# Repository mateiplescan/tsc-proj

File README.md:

# OpenBook &copy; Matei-Bogdan Plescan 2025

## Diagrama bloc

## Randare 3D

## Bill of Materials

| Piesă                                      | Qty                                                                                             | Datasheet | Aprovizionare  |
|----------------------------------------------|---------------------------------------------------------------------------------------------------|----------------|-----------------|
| ADAFRUIT_CHIP-LED0603                        | 1                                                                                           | [Link](https://www.snapeda.com/parts/KP-1608SURCK/Kingbright/datasheet/)      | [Link](https://www.arrow.com/en/products/kp-1608surck/kingbright?utm_campaign=arrow_snapeda_q32020&utm_currency=USD&utm_term=KP-1608SURCK&utm_content=inpart_link_download&region=europe&utm_source=snapeda&utm_medium=aggregator)       |
| SJ                                           | 1                                                                                               | [Link](https://grabcad.com/library/solder-jumpers-1)      | [Link](https://grabcad.com/library/solder-jumpers-1)       |
| ESP32_WROVER_EAGLE-LTSPICE_R0402             | 24                                                                                       | [Link](https://ro.mouser.com/ProductDetail/YAGEO/RC0402FR-07100KL?qs=mnq%2FyloZIXzTlUn7JAHSWg%3D%3D)      | [Link](https://ro.mouser.com/ProductDetail/YAGEO/RC0402FR-07100KL?qs=mnq%2FyloZIXzTlUn7JAHSWg%3D%3D)       |
| ESP32_WROVER_EAGLE-LTSPICE_C0402             | 26                                                           | [Link](https://eu.mouser.com/datasheet/2/447/upy_gphc_x5r_4v_to_50v-3461255.pdf)      | [Link](https://eu.mouser.com/ProductDetail/YAGEO/CC0402MRX5R5BB106?qs=zEY9bCHj09eCmUJdZuS5Lg%3D%3D)       |
| RCL_CT3528                                   | 1                                                                                                 | [Link](https://ro.mouser.com/ProductDetail/KEMET/T491B107M006AT?qs=U312oeP%2FpiHOgyk6KO2m0g%3D%3D)      | [Link](https://ro.mouser.com/ProductDetail/KEMET/T491B107M006AT?qs=U312oeP%2FpiHOgyk6KO2m0g%3D%3D)       |
| 112ATAARR03ATTEND                            | 1                                                                                                 | [Link](https://store.comet.bg/download-file.php?id=27596)      | [Link](https://store.comet.srl.ro/Catalogue/Product/43497/)       |
| ESP32_WROVER_SPARKFUN-DISCRETESEMI_SOT23-3    | 2                                                                                             | [Link](https://www.diodes.com/assets/Datasheets/DMG2305UX.pdf)      | [Link](https://eu.mouser.com/ProductDetail/Diodes-Incorporated/DMG2305UX-7?qs=L1DZKBg7t5F%2FNBHrjfxC%252Bg%3D%3D)       |
| IND_4828-WE-TPC_WRE                         | 1                                                                                                 | [Link](https://www.we-online.com/components/products/datasheet/744043680.pdf)      | [Link](https://eu.mouser.com/ProductDetail/Wurth-Elektronik/744043680?qs=PGXP4M47uW6VkZq%252BkzjrHA%3D%3D)       |
| SOT95P280X125-5N                             | 1                                                                                                | [Link](https://fscdn.rohm.com/en/products/databook/datasheet/ic/power/voltage_detector/bd52xxg-e.pdf)      | [Link](https://eu.mouser.com/ProductDetail/ROHM-Semiconductor/BD5229G-TR?qs=4kLU8WoGk0vvnhrrYwdszw%3D%3D)       |
| MYBUTTON                                     | 2                                                         | [Link](https://www3.panasonic.biz/ac/e_download/control/switch/light-touch/catalog/sw_lt_eng_3529s_side.pdf?f_cd=402906)      | [Link](https://eu.mouser.com/ProductDetail/Panasonic/EVQ-P7L01P?qs=rJ%252BziJWpyszWhhNszc02jQ%3D%3D)       |
| CAPCP3225X100N                               | 1                                                                                        | [Link](https://eu.mouser.com/datasheet/2/360/Seiko_Instruments_MicroBattery_E_20230330_2024Jan_-3561061.pdf)      | [Link](https://eu.mouser.com/ProductDetail/Seiko-Semiconductors/CPH3225A?qs=3etwrb1wR%252BhUOph6lAO7eg%3D%3D)       |
| SOIC127P1032X265-16N                         | 1                                                                                                 | [Link](https://eu.mouser.com/datasheet/2/609/DS3231-3421123.pdf)      | [Link](https://eu.mouser.com/ProductDetail/Analog-Devices-Maxim-Integrated/DS3231SN?qs=1eQvB6Dk1vhUlr8%2FOrV0Fw%3D%3D)       |
| XCVR_ESP32-C6-WROOM-1-N8                    | 1                                                                                                 | [Link](https://eu.mouser.com/datasheet/2/891/Espressif_ESP32_C6_WROOM_1__Datasheet_V0_1_PRELIMI-3239987.pdf)      | [Link](https://eu.mouser.com/ProductDetail/Espressif-Systems/ESP32-C6-WROOM-1-N8?qs=8Wlm6%252BaMh8ST02Gmwp74cw%3D%3D)       |
| ESP32C6_VARISTOR_CT/CN1812                  | 1                                                                                        | [Link](https://www.digikey.ro/en/products/detail/abracon-llc/AMCV-1812H-180-T/4245629)      | [Link](https://www.digikey.ro/en/products/detail/abracon-llc/AMCV-1812H-180-T/4245629)       |
| ESP32_WROVER_AVX---SD0805S020S1R0_AVX_SD0805S020S1R0_0 | 2                                                                                             | [Link](https://eu.mouser.com/datasheet/2/40/schottky-3165252.pdf)      | [Link](https://eu.mouser.com/ProductDetail/KYOCERA-AVX/SD0805S020S1R0?qs=jCA%252BPfw4LHbpkAoSnwrdjw%3D%3D)       |
| ESP32_WROVER_BME680_PSON80P300X300X100-8N    | 1                                                                                           | [Link](https://www.bosch-sensortec.com/media/boschsensortec/downloads/datasheets/bst-bme680-ds001.pdf)      | [Link](https://store.comet.srl.ro/Catalogue/Product/50164/)       |
| ESP32_WROVER_SPARKFUN-IC-POWER_SOT23-5       | 1                                                                                                 | [Link](https://eu.mouser.com/datasheet/2/268/MCP73831_Family_Data_Sheet_DS20001984H-3441711.pdf)      | [Link](https://eu.mouser.com/ProductDetail/Microchip-Technology/MCP73831T-4ADI-OT?qs=hH%252BOa0VZEiBTiqxSV9eepQ%3D%3D)       |
| FH34SRJ24S05SH99                             | 1                                                                                                 | [Link](https://eu.mouser.com/datasheet/2/760/xc6220-3371556.pdf)      | [Link](https://eu.mouser.com/ProductDetail/Torex-Semiconductor/XC6220A331MR-G?qs=AsjdqWjXhJ8ZSWznL1J0gg%3D%3D)       |
| SON50P200X200X80-9N                          | 1                                                                                                 | [Link](https://eu.mouser.com/datasheet/2/609/MAX17048_MAX17049-3469099.pdf)      | [Link](https://eu.mouser.com/ProductDetail/Analog-Devices-Maxim-Integrated/MAX17048G%2bT10?qs=D7PJwyCwLAoGnnn8jEPRBQ%3D%3D)       |
| SOD3716X135N                                 | 3                                                                                         | [Link](https://eu.mouser.com/datasheet/2/40/schottky-3165252.pdf)      | [Link](https://eu.mouser.com/ProductDetail/KYOCERA-AVX/SD0805S020S1R0?qs=jCA%252BPfw4LHbpkAoSnwrdjw%3D%3D)       |
| DIOC1608X36N                                 | 6                                                                           | [Link](https://www.littelfuse.com/assetdocs/pulseguard-esd-suppressors-pgb1-datasheet?assetguid=8a337998-d54d-466b-be4e-dc5bcd1f9321)      | [Link](https://eu.mouser.com/ProductDetail/Littelfuse/PGB1010603MR?qs=gu7KAQ731URLg4GSnNNN7Q%3D%3D)       |
| JST04_1MM_RA                                 | 1                                                                                                 | [Link](https://eu.mouser.com/datasheet/2/813/Qwiic_Connector_Datasheet-1223982.pdf)      | [Link](https://eu.mouser.com/ProductDetail/SparkFun/PRT-14417?qs=wd5RIQLrsJhgdz%2FpmZ%2F3GQ%3D%3D)       |
| SAMACSYS_PARTS_USB4110GFA                    | 1                                                                                                 | [Link](https://eu.mouser.com/datasheet/2/837/GCT_USB4110_Product_Drawing___20k_cycles-3455479.pdf)      | [Link](https://eu.mouser.com/ProductDetail/GCT/USB4110-GF-A?qs=KUoIvG%2F9IlYiZvIXQjyJeA%3D%3D)       |
| SOT65P210X110-3N                             | 1                                                                                                 | [Link](https://www.vishay.com/doc?63399)      | [Link](https://eu.mouser.com/ProductDetail/Vishay-Semiconductors/SI1308EDL-T1-GE3?qs=bX1%252BNvsK%2FBramh9tgpOaEw%3D%3D)       |
| SOT95P280X145-6N                             | 1                                                                                                 | [Link](https://eu.mouser.com/datasheet/2/389/usblc6_2sc6y-1852505.pdf)      | [Link](https://eu.mouser.com/ProductDetail/STMicroelectronics/USBLC6-2SC6Y?qs=gNDSiZmRJS%2FOgDexvXkdow%3D%3D)       |
| SON127P600X800X80-9N                         | 11                                                                                                 | [Link](https://eu.mouser.com/datasheet/2/949/Winbond_W25Q512JV_Datasheet-3240039.pdf)      | [Link](https://eu.mouser.com/ProductDetail/Winbond/W25Q512JVEIQ?qs=l7cgNqFNU1jw6svr3at6tA%3D%3D)       |
| SOT95P280X120-5N                             | 1                                                                                                | [Link](https://eu.mouser.com/datasheet/2/760/xc6220-3371556.pdf)      | [Link](https://eu.mouser.com/ProductDetail/Torex-Semiconductor/XC6220A331MR-G?qs=AsjdqWjXhJ8ZSWznL1J0gg%3D%3D)       |

## Descriere Hardware

OpenBook este bazat pe microcontrollerul ESP32-C6. Dispozitivul integrează un display E-Paper, senzori de mediu, stocare de date pe card SD și memorie flash externă, un ceas de timp real (RTC), management avansat al alimentării cu baterie Li-Po și conector de expansiune Qwiic.

### 1. Microcontroller

* **Componentă:** Modul ESP32-C6-WROOM-1-N8 de la Espressif.
* **Procesor:** Nucleu RISC-V single-core pe 32 de biți, până la 160 MHz.
* **Conectivitate:**
    * Wi-Fi 6 (802.11ax)
    * Bluetooth 5 / Bluetooth Low Energy (BLE)
    * Thread/Zigbee (802.15.4)
* **Memorie:** Include SRAM intern și suportă memorie flash externă (utilizată în design).
* **Interfețe:** Dispune de multiple periferice hardware, inclusiv SPI, I2C, SDIO, USB Serial/JTAG, GPIO, ADC, etc., utilizate extensiv în acest design pentru a comunica cu celelalte componente.
* **Rol:** Acționează ca unitate centrală de procesare, controlând toate celelalte module, colectând date de la senzori, gestionând afișajul, stocarea datelor și comunicațiile wireless.

### 2. Managementul Alimentării

* **Intrare Principală:** Conector USB Type-C.
    * Furnizează 5V (VBUS) pentru alimentarea sistemului și încărcarea bateriei.
    * Include circuite de protecție ESD (USBLC6-2SCISY).
* **Încărcare Baterie:**
    * **Componentă:** MCP73831T-2ACI/OT (Li-Po Battery Charging Controller).
    * **Funcționalitate:** Gestionează procesul de încărcare pentru o baterie de la sursa de 5V (USB).
    * **Indicator Status:** Pinul STAT (conectat la ESP32-C6) indică starea procesului de încărcare. Un LED (CHG_LED) oferă indicație vizuală.
* **Baterie:** Conector standard pentru baterie Li-Po.
* **Regulator de Tensiune:**
    * **Componentă:** XC8220A331MR-G (LDO Voltage Regulator).
    * **Funcționalitate:** Primește tensiune fie de la VBUS (USB 5V), fie de la bateria Li-Po (VBAT, ~3.0V-4.2V) și furnizează o tensiune stabilă de **3.3V** pentru alimentarea ESP32-C6 și a majorității perifericelor.
* **Monitorizare Baterie:**
    * **Componentă:** MAX17048G+T10.
    * **Funcționalitate:** Măsoară tensiunea bateriei și estimează starea de încărcare (SoC) și alte informații relevante despre baterie.
    * **Interfață:** Comunică cu ESP32-C6 prin **I2C**.
* **Supervizor Tensiune și Reset:**
    * **Componentă:** BD5229G-TR (Voltage Supervisor).
    * **Funcționalitate:** Monitorizează tensiunea de 3.3V. Dacă tensiunea scade sub un prag prestabilit, generează un semnal de RESET activ-low pe pinul EN al ESP32-C6, asigurând o pornire și funcționare stabilă. Permite și reset manual prin butonul RESET.

### 3. Afișaj (Display)

* **Tip:** E-Paper Display (EPD).
* **Conector:** FH34SR-245-0.5SH_99 (conector FPC cu 24 pini, pas 0.5mm).
* **Circuit Driver:** Include componente discrete (tranzistori MOSFET precum DMG2305UX-7, drivere de poartă precum 5123-11-GE3) necesare pentru a genera tensiunile și semnalele specifice EPD-urilor.
* **Interfață:** Circuitul driver este controlat de ESP32-C6 prin **SPI**.

### 4. Stocare Date

* **Card SD:**
    * **Slot:** Conector standard pentru card microSD.
    * **Interfață:** Conectat la ESP32-C6 folosind interfața **SPI**. Permite stocarea unor volume mari de date (ex: log-uri, fișiere de configurare, imagini).
* **Memorie Flash Externă:**
    * **Componentă:** W25Q512JVEIQ (NOR Flash, 64 Mbit).
    * **Interfață:** Conectată la ESP32-C6 prin **SPI**.
    * **Rol:** Utilizată pentru stocarea firmware-ului principal, a sistemului de fișiere, a configurațiilor sau a datelor critice.

### 5. Senzori și Timp Real

* **Senzor Ambiental:**
    * **Componentă:** BME688 de la Bosch Sensortec.
    * **Funcționalitate:** Măsoară temperatura, umiditatea relativă, presiunea barometrică și compuși organici volatili (VOC), oferind un indice al calității aerului (IAQ).
    * **Interfață:** Comunică cu ESP32-C6 prin **SPI**.
* **Ceas Timp Real (RTC):**
    * **Componentă:** DS3231SN.
    * **Funcționalitate:** Menține data și ora exactă independent de starea de alimentare a ESP32-C6, datorită unei surse de backup (Supercapacitor CPH3225A - C10). Esențial pentru timestamp-uri precise în log-uri.
    * **Interfață:** Comunică cu ESP32-C6 prin **I2C**.

### 6. Interfață Utilizator și Expansiune

* **Butoane:**
    * **RESET:** Buton tactil conectat la intrarea supervizorului de tensiune (și implicit la pinul EN al ESP32-C6) pentru reset manual.
    * **BOOT (IO9):** Buton tactil conectat la GPIO9. Folosit în mod uzual pentru a pune ESP32 în modul bootloader (pentru programare firmware). Poate fi folosit și ca buton de uz general în aplicație.
    * **CHANGE (IO15):** Buton tactil conectat la GPIO15. Destinat utilizării generale în aplicație (ex: schimbare mod afișaj, trigger acțiune).
* **Conector Expansiune:**
    * **Tip:** Conector Qwiic / Stemma QT (standard SparkFun / Adafruit).
    * **Funcționalitate:** Expune magistrala **I2C** a ESP32-C6 (SDA, SCL), împreună cu 3.3V și GND, permițând conectarea ușoară a numeroase module și senzori externi compatibili.

### 7. Alocarea Pinilor ESP32-C6 (Modul U2)

| **Pin** | **Semnal** | **Componentă** | **Rol** |
|---------|----------------------|----------------|---------|
| EN      | RESET                | Buton Reset    | Intrare pentru resetarea sistemului |
| IO0     | INT_RTC              | RTC DS3231SN   | Întrerupere de la RTC pentru evenimente temporale |
| IO1     | 32KHZ                | RTC DS3231SN   | Semnal de ceas 32kHz de la modulul RTC |
| IO2     | MISO                 | Magistrala SPI | Intrare de date de la periferice SPI |
| IO3     | EPD_BUSY             | Afișaj E-Paper | Monitorizarea stării de disponibilitate a afișajului |
| IO4     | SS_SD                | Card SD        | Selectare chip pentru cardul SD |
| IO5     | EPD_DC               | Afișaj E-Paper | Selectare date/comandă pentru afișaj |
| IO6     | SCK                  | Magistrala SPI | Semnal de ceas pentru comunicația SPI |
| IO7     | MOSI                 | Magistrala SPI | Ieșire de date către periferice SPI |
| IO8     | GPIO8                | Uz general     | Funcții auxiliare |
| IO9     | IO/BOOT              | Buton Boot     | Selectare mod boot/programare |
| IO10    | EPD_CS               | Afișaj E-Paper | Selectare chip pentru afișajul E-Paper |
| IO11    | FLASH_CS             | Flash NOR extern | Selectare chip pentru memoria flash |
| IO12    | USB_D-               | Interfață USB  | Linie de date USB negativă |
| IO13    | USB_D+               | Interfață USB  | Linie de date USB pozitivă |
| IO15    | IO/CHANGE            | Buton Change   | Detectare schimbare de stare |
| IO16/TXD0 | TX                 | Debug Serial   | Transmitere UART |
| IO17/RXD0 | RX                 | Debug Serial   | Recepție UART |
| IO18    | RTC_RST              | RTC DS3231SN   | Control reset pentru RTC |
| IO19    | I2C_PW               | Magistrala I2C | Control alimentare pentru dispozitivele I2C |
| IO20    | EPD_3V3_C            | Afișaj E-Paper | Control alimentare pentru afișaj |
| IO21    | SDA                  | Magistrala I2C | Linie de date I2C |
| IO22    | SCL                  | Magistrala I2C | Linie de ceas I2C |
| IO23    | EPD_RST              | Afișaj E-Paper | Control reset pentru afișaj |

### Justificarea utilizării pinilor ESP32-C6 în DeskAssistant v19:

Alocarea pinilor ESP32-C6 în acest design a fost făcută cu atenție pentru a optimiza funcționalitatea și a gestiona eficient resursele limitate ale microcontrolerului:

- **Grupare funcțională**: Pinii sunt organizați pentru a grupa funcționalitățile similare. De exemplu, pinii pentru interfața SPI (MISO, MOSI, SCK) sunt plasați strategic pentru a facilita rutarea PCB și a reduce interferențele.

- **Pini speciali pentru interfețe standard**: IO21 și IO22 sunt utilizați pentru SDA și SCL, fiind pinii standard recomandați pentru I2C pe ESP32. Similar, IO16 și IO17 sunt utilizați pentru funcțiile UART datorită implementării hardware dedicate.

- **Pini GPIO cu funcționalități speciale pentru afișajul E-Paper**: Afișajul E-Paper necesită control complex, de aceea are alocați mai mulți pini (EPD_BUSY, EPD_DC, EPD_CS, EPD_RST, EPD_3V3_C) pentru funcționarea corectă și eficientă.

- **Management energie**: Pinul IO19 este dedicat controlului alimentării dispozitivelor I2C, permițând economisirea energiei prin oprirea acestora când nu sunt utilizate, esențial pentru un dispozitiv alimentat de baterie.

- **Comunicație cu memoria externă**: Memoria flash NOR necesită acces rapid și fiabil, de aceea utilizează un pin dedicat pentru selecție (IO11) pe lângă liniile standard SPI.

- **Conectivitate USB**: Pinii IO12 și IO13 sunt utilizați pentru USB_D- și USB_D+, permițând conectivitatea directă prin USB fără circuite externe suplimentare.

- **Integrare RTC**: Modulul RTC are multiple conexiuni (INT_RTC, 32KHZ, RTC_RST) pentru o funcționalitate completă, oferind atât ceas precis, cât și capacitatea de a trezi microcontrolerul din starea de somn profund.

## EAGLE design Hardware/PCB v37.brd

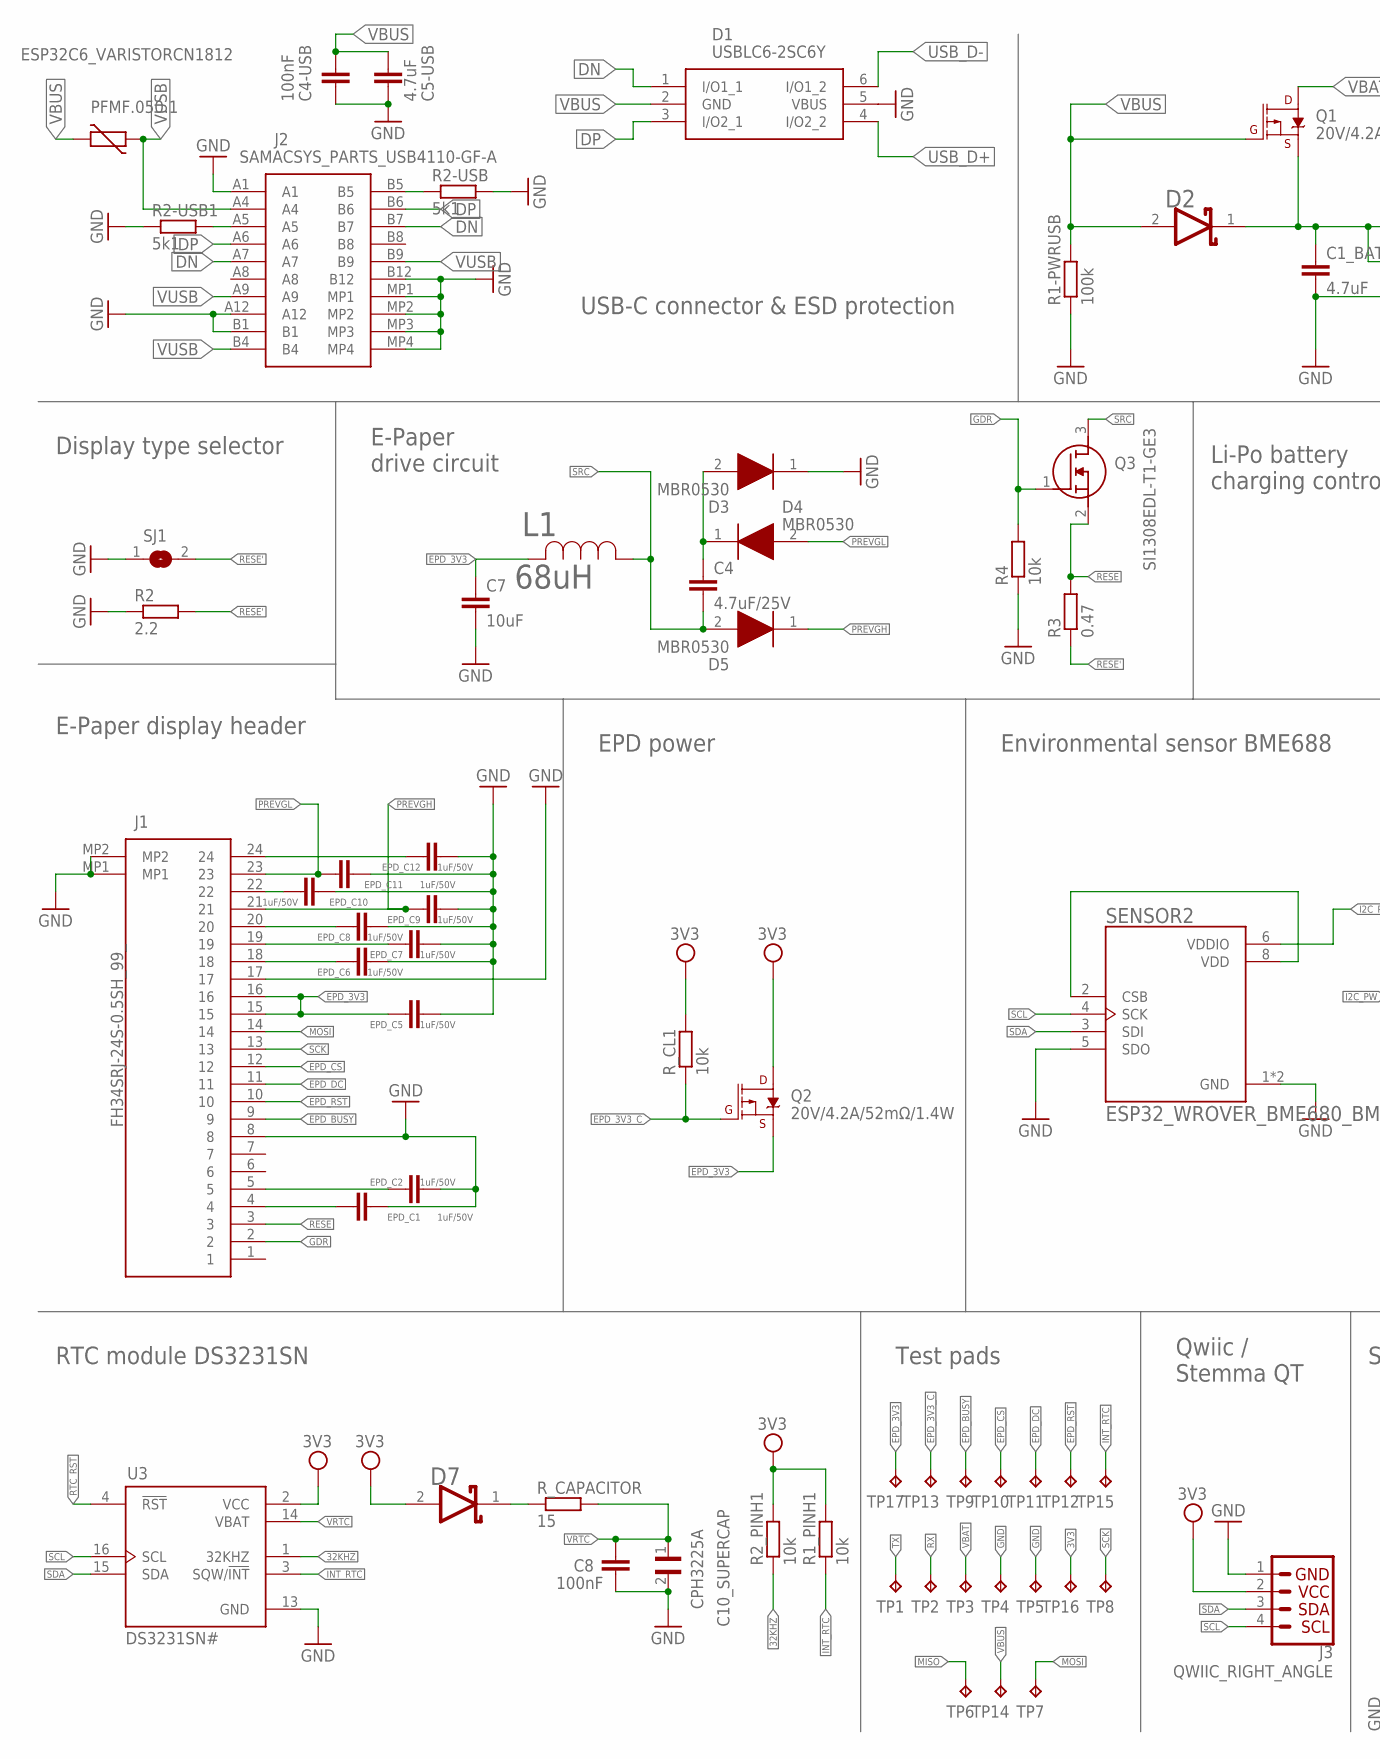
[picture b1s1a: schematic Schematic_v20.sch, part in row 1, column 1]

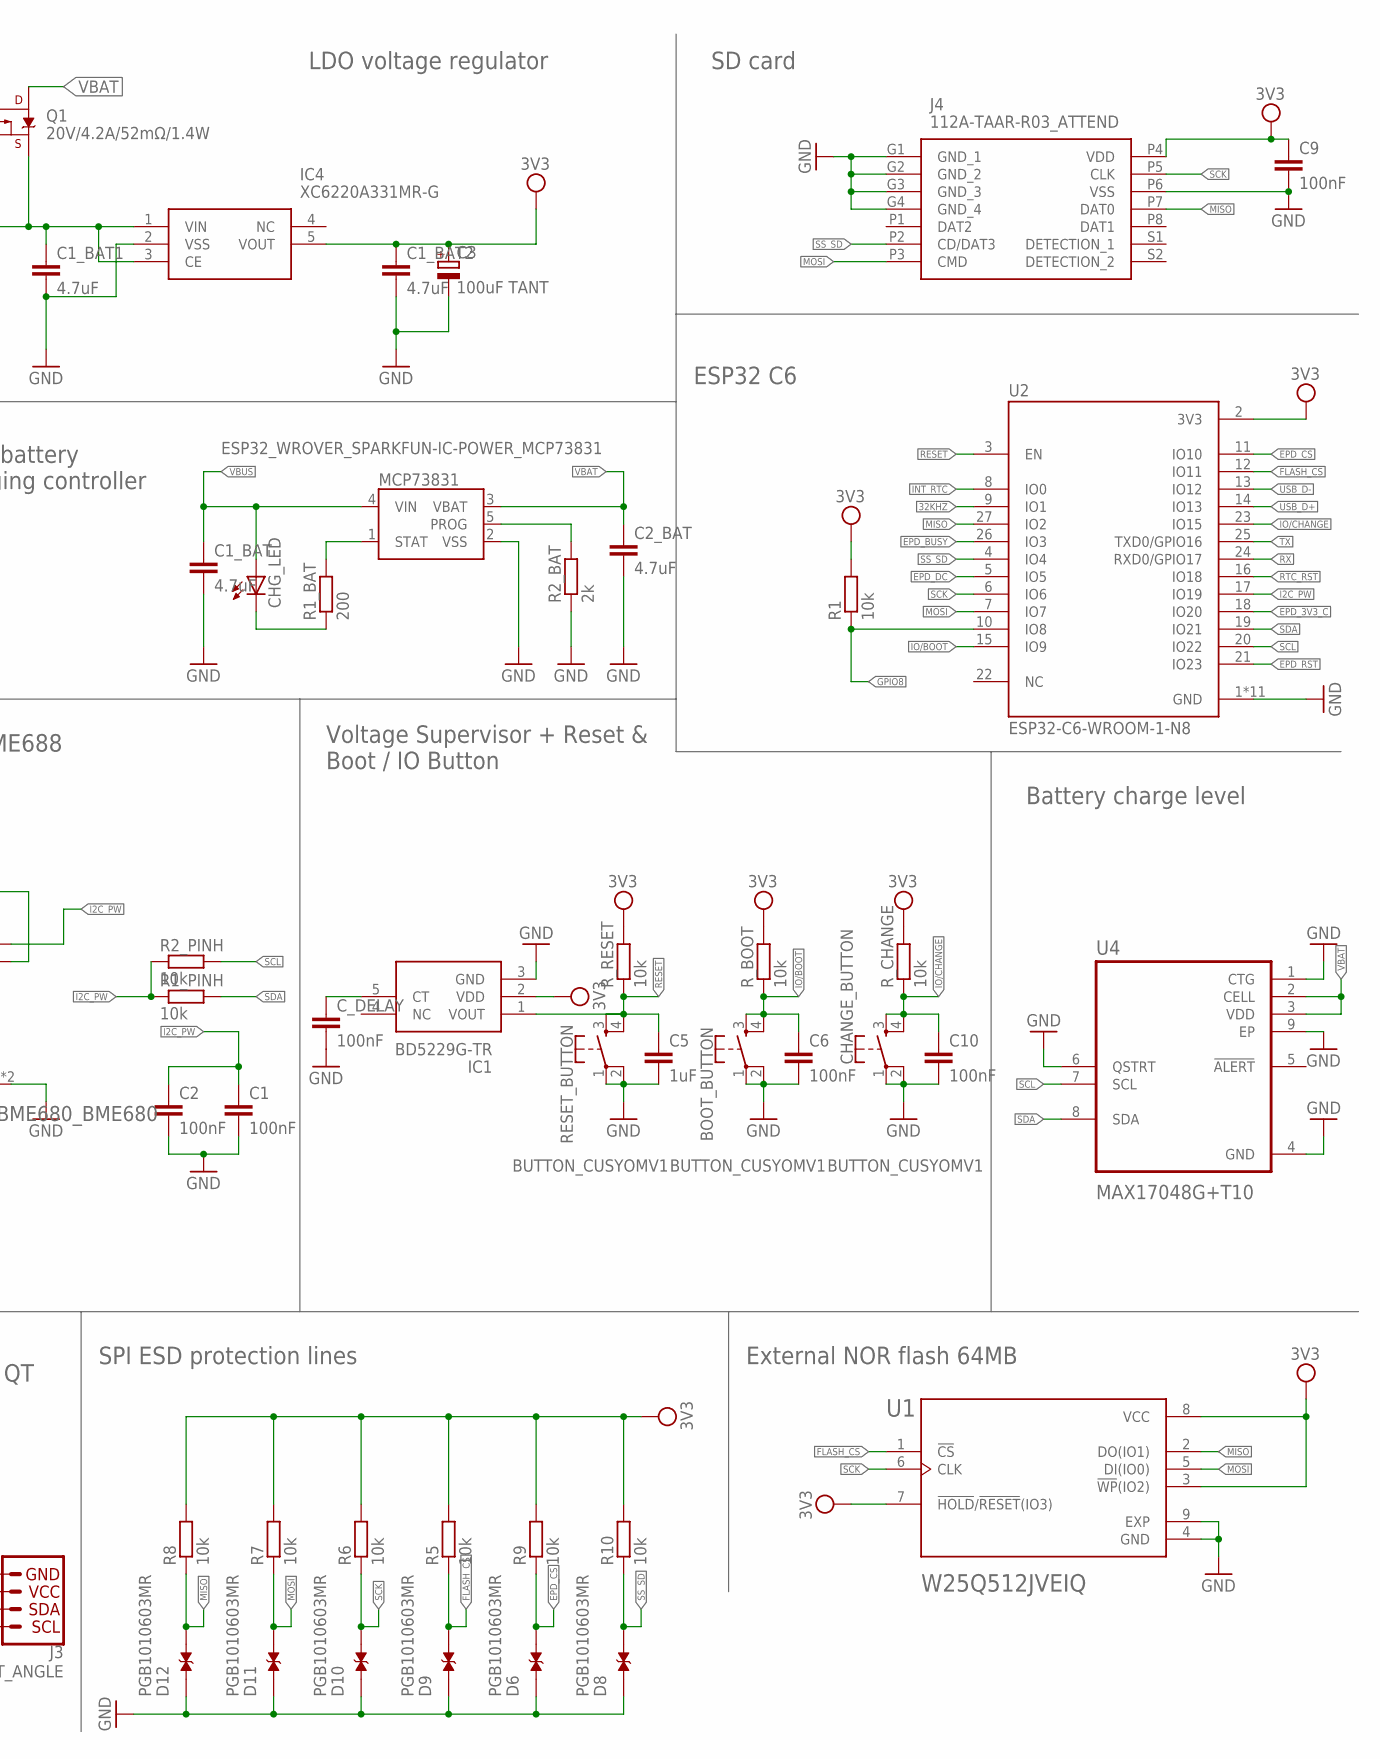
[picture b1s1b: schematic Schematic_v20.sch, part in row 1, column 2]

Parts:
BOOT_BUTTON: BUTTON_CUSYOMV1; MYBUTTON
C1, C2, C6, C8, C9, C10: 100nF; EAGLE-LTSPICE_C0402
C1_BAT, C2_BAT: 4.7uF; EAGLE-LTSPICE_C0402
C1_BAT1, C1_BAT2, C5-USB: 4.7uF; ESP32_WROVER_EAGLE-LTSPICE_C0402
C3: 100uF TANT; RCL_CT3528
C4: 4.7uF/25V; EAGLE-LTSPICE_C0402
C4-USB: 100nF; ESP32_WROVER_EAGLE-LTSPICE_C0402
C5: 1uF; EAGLE-LTSPICE_C0402
C7: 10uF; EAGLE-LTSPICE_C0402
C10_SUPERCAP: CPH3225A; CAPCP3225X100N
CHANGE_BUTTON: BUTTON_CUSYOMV1; MYBUTTON
CHG_LED: ADAFRUIT_LEDCHIP-LED0603; ADAFRUIT_CHIP-LED0603
C_DELAY: 100nF; EAGLE-LTSPICE_C0402
D1: USBLC6-2SC6Y; SOT95P280X145-6N
D2, D7: ESP32_WROVER_AVX---SD0805S020S1R0_AVX_SD0805S020S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; ESP32_WROVER_AVX---SD0805S020S1R0_AVX_SD0805S020S1R0_0
D3, D4, D5: MBR0530; SOD3716X135N
D6, D8, D9, D10, D11, D12: PGB1010603MR; DIOC1608X36N
EPD_C1, EPD_C2, EPD_C5, EPD_C6, EPD_C7, EPD_C8, EPD_C9, EPD_C10, EPD_C11, EPD_C12: 1uF/50V; EAGLE-LTSPICE_C0402
IC1: BD5229G-TR; SOT95P280X125-5N
IC4: XC6220A331MR-G; SOT95P280X120-5N
J1: FH34SRJ-24S-0.5SH_99_; FH34SRJ24S05SH99
J2: SAMACSYS_PARTS_USB4110-GF-A; SAMACSYS_PARTS_USB4110GFA
J3: QWIIC_RIGHT_ANGLE; JST04_1MM_RA
J4: 112A-TAAR-R03_ATTEND; 112ATAARR03ATTEND
L1: 68uH; IND_4828-WE-TPC_WRE
MCP73831: ESP32_WROVER_SPARKFUN-IC-POWER_MCP73831; ESP32_WROVER_SPARKFUN-IC-POWER_SOT23-5
PFMF.050.1: ESP32C6_VARISTORCN1812; ESP32C6_VARISTOR_CT/CN1812
Q1, Q2: 20V/4.2A/52mΩ/1.4W; ESP32_WROVER_SPARKFUN-DISCRETESEMI_SOT23-3
Q3: SI1308EDL-T1-GE3; SOT65P210X110-3N
R1, R1_PINH, R1_PINH1, R2_PINH, R2_PINH1, R4, R5, R6, R7, R8, R9, R10: 10k; ESP32_WROVER_EAGLE-LTSPICE_R0402
R1-PWRUSB: 100k; ESP32_WROVER_EAGLE-LTSPICE_R0402
R1_BAT: 200; ESP32_WROVER_EAGLE-LTSPICE_R0402
R2: 2.2; ESP32_WROVER_EAGLE-LTSPICE_R0402
R2-USB, R2-USB1: 5k1; ESP32_WROVER_EAGLE-LTSPICE_R0402
R2_BAT: 2k; ESP32_WROVER_EAGLE-LTSPICE_R0402
R3: 0.47; ESP32_WROVER_EAGLE-LTSPICE_R0402
RESET_BUTTON: BUTTON_CUSYOMV1; MYBUTTON
R_BOOT: 10k; ESP32_WROVER_EAGLE-LTSPICE_R0402
R_CAPACITOR: 15; ESP32_WROVER_EAGLE-LTSPICE_R0402
R_CHANGE: 10k; ESP32_WROVER_EAGLE-LTSPICE_R0402
R_CL1: 10k; ESP32_WROVER_EAGLE-LTSPICE_R0402
R_RESET: 10k; ESP32_WROVER_EAGLE-LTSPICE_R0402
SENSOR2: ESP32_WROVER_BME680_BME680; ESP32_WROVER_BME680_PSON80P300X300X100-8N
SJ1: SJ
TP1, TP2, TP3, TP4, TP5, TP6, TP7, TP8, TP9, TP10, TP11, TP12, TP13, TP14, TP15, TP16, TP17: TPTP20R; TP20R
U1: W25Q512JVEIQ; SON127P600X800X80-9N
U2: ESP32-C6-WROOM-1-N8; XCVR_ESP32-C6-WROOM-1-N8
U3: DS3231SN#; SOIC127P1032X265-16N
U4: MAX17048G+T10; SON50P200X200X80-9N

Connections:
3V3: C1_BAT2.1, C3.+, C9.1, D7.2 (ANODE), IC1.2 (VDD), IC4.5 (VOUT), J3.2, J4.P4 (VDD), Q2.3 (D), R1.2, R1_PINH1.2, R2_PINH1.2, R5.2, R6.2, R7.2, R8.2, R9.2, R10.2, R_BOOT.2, R_CHANGE.2, R_CL1.2, R_RESET.2, TP16.TP, U1.3 (!WP!(IO2)), U1.7 (!HOLD!/!RESET!(IO3)), U1.8 (VCC), U2.2 (3V3), U3.2 (VCC)
32KHZ: R2_PINH1.1, U2.9 (IO1), U3.1 (32KHZ)
DN: D1.1 (I/O1_1), J2.A7, J2.B7
DP: D1.3 (I/O2_1), J2.A6, J2.B6
EPD_3V3: C7.1, EPD_C5.1, J1.15, J1.16, L1.2, Q2.2 (S), TP17.TP
EPD_3V3_C: Q2.1 (G), R_CL1.1, TP13.TP, U2.18 (IO20)
EPD_BUSY: J1.9, TP9.TP, U2.26 (IO3)
EPD_CS: D6.2, J1.12, R9.1, TP10.TP, U2.11 (IO10)
EPD_DC: J1.11, TP11.TP, U2.5 (IO5)
EPD_RST: J1.10, TP12.TP, U2.21 (IO23)
FLASH_CS: D9.2, R5.1, U1.1 (!CS), U2.12 (IO11)
GDR: J1.2, Q3.1 (G), R4.2
GND: BOOT_BUTTON.1, BOOT_BUTTON.2, C1.2, C1_BAT.2, C1_BAT1.2, C1_BAT2.2, C2.2, C2_BAT.2, C3.-, C4-USB.2, C5.2, C5-USB.2, C6.2, C7.2, C8.2, C9.2, C10.2, C10_SUPERCAP.2, CHANGE_BUTTON.1, CHANGE_BUTTON.2, C_DELAY.2, D1.5 (VBUS), D3.1 (K), D6.1, D8.1, D9.1, D10.1, D11.1, D12.1, EPD_C1.2, EPD_C2.2, EPD_C5.2, EPD_C6.2, EPD_C7.2, EPD_C8.2, EPD_C9.2, EPD_C10.2, EPD_C11.2, EPD_C12.2, IC1.3 (GND), IC4.2 (VSS), J1.8, J1.17, J1.MP1, J1.MP2, J2.A1, J2.A12, J2.B1, J2.B12, J2.MP1, J2.MP2, J2.MP3, J2.MP4, J3.1, J4.G1 (GND_1), J4.G2 (GND_2), J4.G3 (GND_3), J4.G4 (GND_4), J4.P6 (VSS), MCP73831.2 (VSS), R1-PWRUSB.1, R2.1, R2-USB.2, R2-USB1.1, R2_BAT.1, R4.1, RESET_BUTTON.1, RESET_BUTTON.2, SENSOR2.1 (GND), SENSOR2.5 (SDO), SENSOR2.7 (GND), SJ1.1, TP4.TP, TP5.TP, U1.4 (GND), U1.9 (EXP), U2.1 (GND), U2.28 (GND), U2.29_1 (GND), U2.29_2 (GND), U2.29_3 (GND), U2.29_4 (GND), U2.29_5 (GND), U2.29_6 (GND), U2.29_7 (GND), U2.29_8 (GND), U2.29_9 (GND), U3.13 (GND), U4.1 (CTG), U4.4 (GND), U4.6 (QSTRT), U4.9 (EP)
GPIO8: R1.1, U2.10 (IO8)
I2C_PW: C1.1, C2.1, R1_PINH.1, R2_PINH.1, SENSOR2.6 (VDDIO), U2.17 (IO19)
INT_RTC: R1_PINH1.1, TP15.TP, U2.8 (IO0), U3.3 (SQW/!INT)
IO/BOOT: BOOT_BUTTON.3, BOOT_BUTTON.4, C6.1, R_BOOT.1, U2.15 (IO9)
IO/CHANGE: C10.1, CHANGE_BUTTON.3, CHANGE_BUTTON.4, R_CHANGE.1, U2.23 (IO15)
MISO: D12.2, J4.P7 (DAT0), R8.1, TP6.TP, U1.2 (DO(IO1)), U2.27 (IO2)
MOSI: D11.2, J1.14, J4.P3 (CMD), R7.1, TP7.TP, U1.5 (DI(IO0)), U2.7 (IO7)
unnamed: J2.A5, R2-USB1.2
unnamed: J2.B5, R2-USB.1
unnamed: SENSOR2.2 (CSB), SENSOR2.8 (VDD)
unnamed: EPD_C6.1, J1.18
unnamed: C1_BAT1.1, D2.1 (CATHODE), IC4.1 (VIN), IC4.3 (CE), Q1.2 (S)
unnamed: EPD_C7.1, J1.19
unnamed: EPD_C8.1, J1.20
unnamed: C4.1, D3.2 (A), D4.1 (K)
unnamed: EPD_C10.1, J1.22
unnamed: EPD_C12.1, J1.24
unnamed: C_DELAY.1, IC1.5 (CT)
unnamed: MCP73831.1 (STAT), R1_BAT.2
unnamed: CHG_LED.C, R1_BAT.1
unnamed: MCP73831.5 (PROG), R2_BAT.2
unnamed: D7.1 (CATHODE), R_CAPACITOR.1
unnamed: EPD_C1.1, J1.4
unnamed: EPD_C2.1, J1.5
PREVGH: D5.1 (K), EPD_C9.1, J1.21
PREVGL: D4.2 (A), EPD_C11.1, J1.23
RESE: J1.3, Q3.2 (S), R3.2
RESE': R2.2, R3.1, SJ1.2
RESET: C5.1, IC1.1 (VOUT), RESET_BUTTON.3, RESET_BUTTON.4, R_RESET.1, U2.3 (EN)
RTC_RST: U2.16 (IO18), U3.4 (!RST)
RX: TP2.TP, U2.24 (RXD0/GPIO17)
SCK: D10.2, J1.13, J4.P5 (CLK), R6.1, TP8.TP, U1.6 (CLK), U2.6 (IO6)
SCL: J3.4, R2_PINH.2, SENSOR2.4 (SCK), U2.20 (IO22), U3.16 (SCL), U4.7 (SCL)
SDA: J3.3, R1_PINH.2, SENSOR2.3 (SDI), U2.19 (IO21), U3.15 (SDA), U4.8 (SDA)
SRC: C4.2, D5.2 (A), L1.1, Q3.3 (D)
SS_SD: D8.2, J4.P2 (CD/DAT3), R10.1, U2.4 (IO4)
TX: TP1.TP, U2.25 (TXD0/GPIO16)
USB_D+: D1.4 (I/O2_2), U2.14 (IO13)
USB_D-: D1.6 (I/O1_2), U2.13 (IO12)
VBAT: C2_BAT.1, MCP73831.3 (VBAT), Q1.3 (D), TP3.TP, U4.2 (CELL), U4.3 (VDD)
VBUS: C1_BAT.1, C4-USB.1, C5-USB.1, CHG_LED.A, D1.2 (GND), D2.2 (ANODE), MCP73831.4 (VIN), PFMF.050.1.2, Q1.1 (G), R1-PWRUSB.2, TP14.TP
VRTC: C8.1, C10_SUPERCAP.1, R_CAPACITOR.2, U3.14 (VBAT)
VUSB: J2.A4, J2.A9, J2.B4, J2.B9, PFMF.050.1.1

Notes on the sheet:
USB-C connector & ESD protection
LDO voltage regulator
SD card
ESP32 C6
Li-Po battery charging controller
E-Paper drive circuit
Display type selector
E-Paper display header
EPD power
Environmental sensor BME688
Voltage Supervisor + Reset & Boot / IO Button
Battery charge level
RTC module DS3231SN
Test pads
Qwiic / Stemma QT
SPI ESD protection lines
External NOR flash 64MB

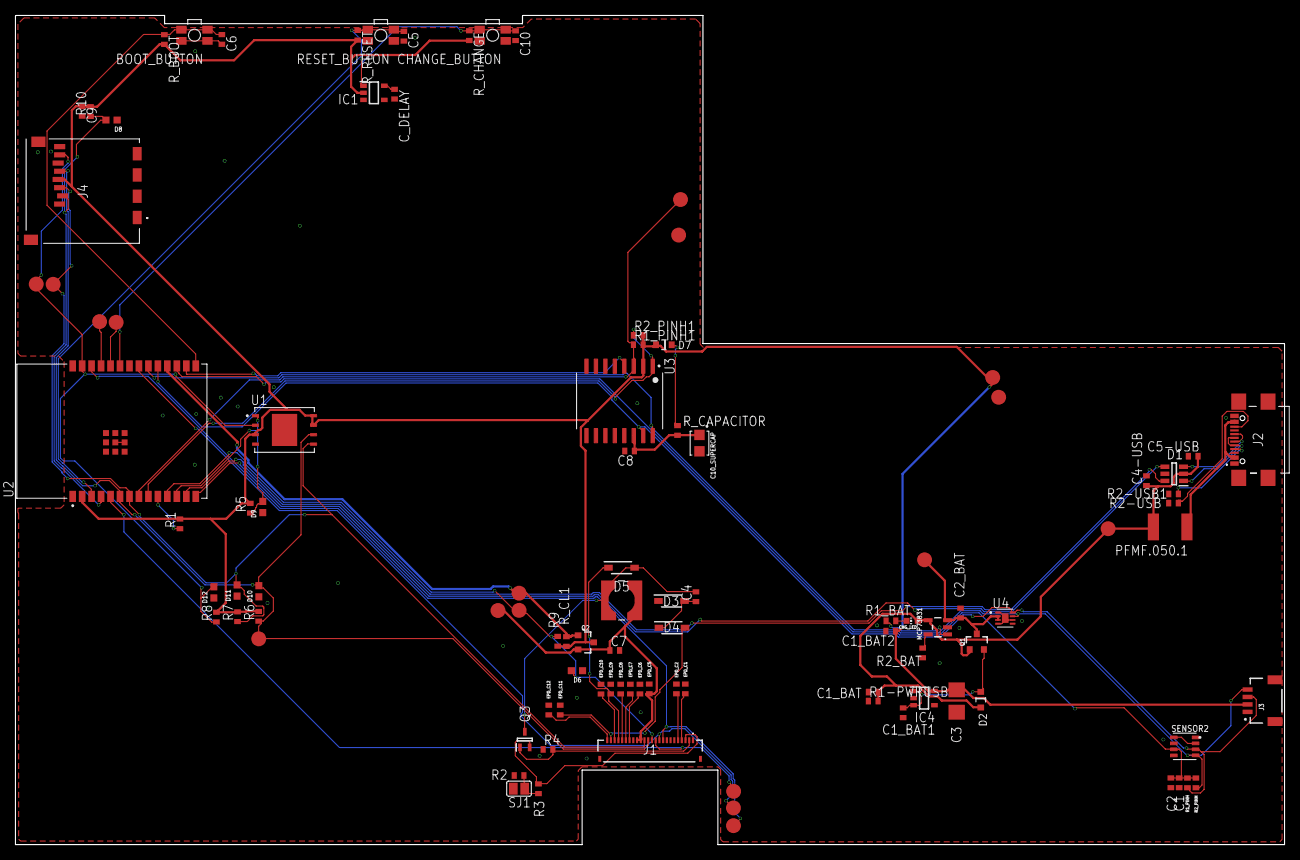
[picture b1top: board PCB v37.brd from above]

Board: 2 copper layers, 170.2 x 111.2 mm, 103 parts (0 on the bottom side), 56 nets.

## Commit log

2025-04-06 Upload documents.
2025-04-06 Create LICENSE
2025-04-06 Update README.md - bom
2025-04-06 Added block diagram and video with exploded view
2025-04-06 Rename Diagrama bloc.png to diagramabloc.png
2025-04-06 Rename Full product - exploded view v1.mp4 to explodedview.mp4
2025-04-06 Update mp4
2025-04-14 Fix issues

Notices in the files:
parts and their libraries:
COPYRIGHT: Copyright (C) 2024 Ultra Librarian. All rights reserved.
